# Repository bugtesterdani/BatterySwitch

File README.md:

# BatterySwitch – Automatischer 2-Akku-Umschalter (58–72 V, 40 A)

Automatische Umschaltung zwischen zwei Akkus (Batterie 1: 50 Ah, Batterie 2: 30 Ah)
in einem **72-V-System** (ca. 71,x V Ladeschluss, ca. 58 V Entladeschluss — z. B.
17s-Li-Ion oder 20s-LiFePO4) durch **direkten Vergleich der beiden Akkuspannungen**
(differentiell, keine feste Umschaltschwelle). Die Umschaltung erfolgt verschleißfrei
über Leistungs-MOSFETs (ausgelegt für ca. 40 A Dauerstrom). Beide Umschalt-Offsets
sind **über je ein Potentiometer getrennt einstellbar**.

## Funktionsprinzip

- Zustand **„Akku 1 aktiv“**: Auf Akku 2 wird umgeschaltet, sobald
  `U(Akku 1) < U(Akku 2) − Δ1` — Δ1 einstellbar mit Poti 1 (ca. 0,4 … 2,9 V).
- Zustand **„Akku 2 aktiv“**: Zurückgeschaltet wird, sobald
  `U(Akku 2) < U(Akku 1) − Δ2` — Δ2 einstellbar mit Poti 2 (unabhängig nachjustierbar).
- Zusätzlich wirkt eine **feste Zusatzhysterese** (ca. 0,1 … 0,8 V je Richtung,
  abhängig von den Poti-Stellungen). Das gesamte Umschaltfenster beträgt damit
  `Δ1 + Δ2` (typisch 2 … 4 V) — die Schaltung schaltet selten, und der
  Stützkondensator am Ausgang wird durch Umschalt-Totzeiten kaum belastet.
- Beim Leerfahren wechseln sich die Akkus automatisch ab und werden gemeinsam
  entladen; wird einer der Akkus geladen, übernimmt er automatisch die Last.

```
 BAT1 (50Ah, 72V) o──[Sicherung 50A/80VDC]──┤ MOSFET-Schalter S1 ├──┐
      │ Sense                                                        ├──o LAST +
 BAT2 (30Ah, 72V) o──[Sicherung 50A/80VDC]──┤ MOSFET-Schalter S2 ├──┘
      │ Sense                                          ▲
      ▼                                                │
  Differenzkomparator (U1 ⇄ U2) ───────────────────────┘
  Δ1-Poti · Δ2-Poti · Photovoltaik-Gate-Treiber · Break-before-make
```

## Eckdaten

| Parameter                  | Wert                                        |
|----------------------------|---------------------------------------------|
| Systemspannung             | 58 … 72 V DC                                |
| Dauerstrom                 | 40 A (Spitze kurzzeitig höher)              |
| Schaltelemente             | antiserielle N-Kanal-MOSFETs je Zweig (IRF100P219, TO-247, 100 V, ≤ 2 mΩ) |
| Verlustleistung bei 40 A   | ca. 7 W je Zweig (1 Paar) bzw. 3,5 W (2 Paare parallel, empfohlen) → Kühlkörper |
| Gate-Ansteuerung           | Photovoltaik-Treiber VOM1271 (potentialfrei, inhärent break-before-make) |
| Umschaltkriterium          | Differenz U1 − U2 (kein fester Spannungswert) |
| Δ1 (auf Akku 2 schalten)   | Poti 1, ca. 0,4 … 2,9 V                     |
| Δ2 (auf Akku 1 zurück)     | Poti 2, ca. 0,4 … 2,9 V                     |
| Zusatzhysterese (fest)     | ca. 0,1 … 0,8 V je Richtung                 |
| Umschalt-Totzeit           | 5 … 10 ms (Akkus werden nie parallel geschaltet) |
| Eigenverbrauch Steuerung   | ca. 25 mA (≈ 1,8 W, ≈ 0,6 Ah/Tag)           |

## Dokumentation

| Dokument | Inhalt |
|----------|--------|
| [hardware/BatterySwitch.kicad_sch](hardware/BatterySwitch.kicad_sch) | **KiCad-Schaltplan** (KiCad 6/7/8/9, direkt zu öffnen) — Vorschau: [hardware/preview.svg](hardware/preview.svg) |
| [hardware/BatterySwitch_Steuerplatine.kicad_pcb](hardware/BatterySwitch_Steuerplatine.kicad_pcb) | **Platinenlayout Steuerplatine** (112×92 mm, 2 Lagen, geroutet) — Vorschau: [hardware/preview_pcb.svg](hardware/preview_pcb.svg) |
| [docs/schaltung.md](docs/schaltung.md) | Vollständige Schaltungsbeschreibung, Schaltbilder, Dimensionierung und Formeln |
| [docs/stueckliste.md](docs/stueckliste.md) | Stückliste (BOM) mit Bauteilwerten und Alternativen |
| [docs/bestellliste.md](docs/bestellliste.md) | Bestellliste mit Händlern, Links und ca.-Preisen inkl. MwSt |
| [docs/aufbau-und-abgleich.md](docs/aufbau-und-abgleich.md) | Aufbauhinweise, Verkabelung, Nullabgleich und Einstellen von Δ1/Δ2 |

## Sicherheitshinweise

- **72 V DC ist keine Schutzkleinspannung.** Berührungsschutz vorsehen, nicht
  unter Spannung arbeiten, DC-Lichtbögen beim Trennen unter Last beachten.
- **Die Minusleitungen beider Akku-Stecker werden im Umschalter-Kabelbaum mit
  dem Fahrzeug-Minus verbunden** (gemeinsame Masse nur im Kabelbaum – an den
  Akkus wird nichts geändert, Einzelbetrieb ohne Board bleibt möglich).
  Geschaltet wird ausschließlich der Pluspfad (High-Side).
- Jeder Akku-Anschluss wird **direkt an der Anschlussklemme mit 50 A abgesichert** — Sicherungen mit
  **≥ 80 V DC-Zulassung** (z. B. gPV 14×51). Kfz-Sicherungen (MIDI/MEGA/ANL,
  32 V) sind ungeeignet. Die Sense-Leitungen separat mit 100 mA absichern.
- Leitungsquerschnitt für den Lastpfad: mindestens **10 mm²** bei 40 A. Die beiden
  Sense-Abgriffe direkt an den Anschlussklemmen der Akku-Stecker (vor F1/F2),
  jeweils mit 100 mA abgesichert; beide Akkuzuleitungen gleich ausführen.
- Während der Umschaltung ist die Last für 5 … 10 ms stromlos
  (Break-before-make). Motorcontroller mit eigenem Zwischenkreis stört das nicht.
- Die Schaltung vergleicht nur **relativ** — es gibt keinen absoluten
  Tiefentladeschutz. Die BMS der Akkus bleiben die letzte Schutzinstanz
  (siehe „Grenzen“ in der Schaltungsbeschreibung).

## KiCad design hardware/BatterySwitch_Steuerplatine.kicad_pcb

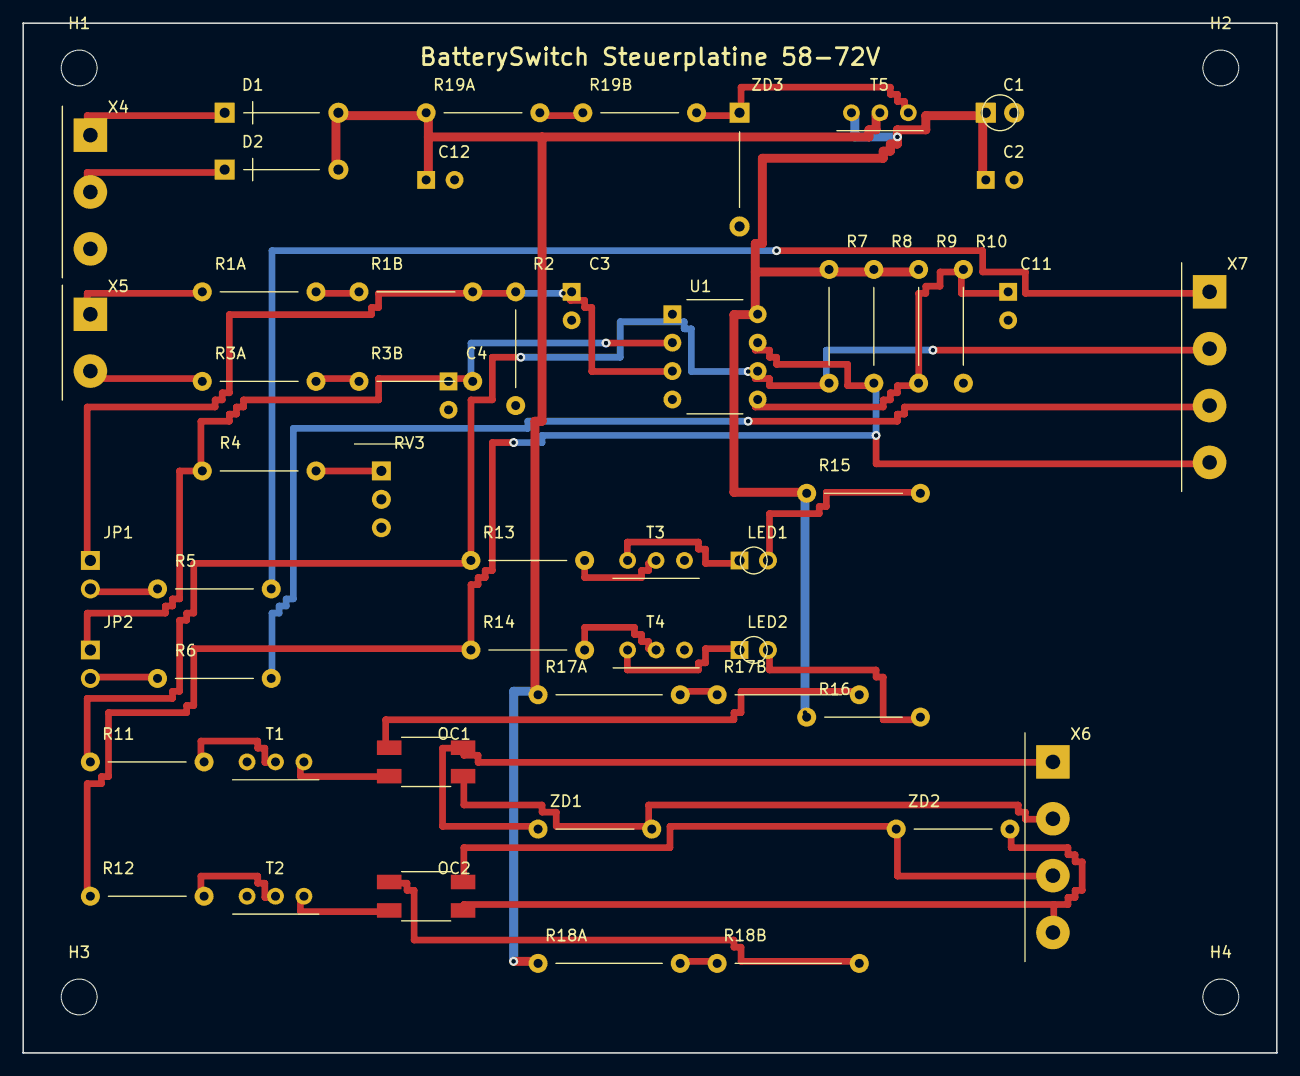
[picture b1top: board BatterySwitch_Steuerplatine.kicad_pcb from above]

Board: 2 copper layers, 112.0 x 92.0 mm, 56 parts (0 on the bottom side), 39 nets.

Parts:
C1: 100u/25V; ELKO
C2: 100n; RAD
C3, C4, C11: 100n; RADV
C12: 100n/100V; RAD
D1, D2: 1N5819; DO41_AK
H1, H2, H3, H4: M3; MH32
JP1: Abgleich D1; HDR2
JP2: Abgleich D2; HDR2
LED1: gruen; LED3
LED2: gelb; LED3
OC1, OC2: VOM1271; SOP4
R1A, R1B, R3A, R3B: 27k 1%; AXH
R2: 2k0 1%; AXV
R4: 1k8 1%; AXH
R5, R6: 150k; AXH
R7, R8: 3k3; AXV
R9, R10: 47k; AXV
R11, R12: 27k; AXH
R13, R14: 330k; AXH
R15, R16: 2k2; AXH
R17A, R17B, R18A, R18B: 3k3/1W; AXH1W
R19A, R19B: 5k6/0,5W; AXH
RV3: 500R 25G; TRIM
T1, T2: MPSA42; TO92_EBC
T3, T4: BC547B; TO92_CBE
T5: MJE340; TO126_ECB
U1: LM393; DIP8
X4: V+ Eingaenge: B1F B2F GND; TERM3
X5: Sense: S1 S2; TERM2
X6: Gates: G1 SK1 G2 SK2; TERM4
X7: Potis: NJ2 OUT NK2 NOUT; TERM4
ZD1, ZD2: 15V; AXH
ZD3: 13V; DO41V

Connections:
A1: OC1.1, R17B.2
A2: OC2.1, R18B.2
B1F: D1.2, X4.1
B2F: D2.2, X4.2
G1: OC1.4, X6.1, ZD1.1
G2: OC2.4, X6.3, ZD2.1
GND: C1.2, C2.2, C3.2, C4.2, C11.2, C12.2, R2.2, R10.2, RV3.2, RV3.3, T1.3, T2.3, T3.3, T4.3, U1.4, X4.3, ZD3.2
K1: OC1.2, T1.2
K2: OC2.2, T2.2
KA: C3.1, JP1.1, R1B.2, R2.1, U1.3
KB: C4.1, JP2.1, R3B.2, R4.1, U1.2
LED1A: LED1.2, R15.2
LED1K: LED1.1, T3.2
LED2A: LED2.2, R16.2
LED2K: LED2.1, T4.2
N1A: R1A.2, R1B.1
N3A: R3A.2, R3B.1
N17: R17A.2, R17B.1
N18: R18A.2, R18B.1
N19: R19A.2, R19B.1
NJ1: JP1.2, R5.1
NJ2: R5.2, X7.1
NK1: JP2.2, R6.1
NK2: R6.2, X7.3
NOUT: R8.2, R12.1, R14.1, U1.7, X7.4
OUT: R7.2, R11.1, R13.1, U1.1, U1.6, X7.2
RVT: R4.2, RV3.1
S1: R1A.1, X5.1
S2: R3A.1, X5.2
SK1: OC1.3, X6.2, ZD1.2
SK2: OC2.3, X6.4, ZD2.2
T1B: R11.2, T1.1
T2B: R12.2, T2.1
T3B: R13.2, T3.1
T4B: R14.2, T4.1
V+: C12.1, D1.1, D2.1, R17A.1, R18A.1, R19A.1, T5.2
VCC: C1.1, C2.1, R7.1, R8.1, R9.1, R15.1, R16.1, T5.3, U1.8
VM: C11.1, R9.2, R10.1, U1.5
ZDK: R19B.2, T5.1, ZD3.1
